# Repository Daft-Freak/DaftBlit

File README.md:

# DaftBlit
It's... a handheld console?

## Boards
- [Gamepads](https://github.com/Daft-Freak/py32-i2c-gamepad) (x2)
- `board/extra-buttons`: "Start/Select" buttons
- `board/display`: "Display" / main baard (has some sound/backlight issues)

## 3D Printed Parts
- `abxy.stl` A/B/X/Y buttons (x4)
- `console28-back.stl` back half of case
- `console28-front.stl` front half of case, should be printed face down
- `console28-dbg-cover` cover for debug port access
- `controller-mod-back.stl`/`controller-mod-front.stl` modifiers for multi-colour printing
- `dpad.stl` dpad, requires supports and a bit tricky to print
- `on-off-flat.stl` power button
- `start-select.stl` start/select buttons, requires supports and is very small (x2)

## Other hardware
- Button pads: 2x the dpad part from a GBA SP set.
- LCD: https://www.aliexpress.com/item/1005009128815676.html (2.8 inch 40 pin 240x320 ST7789)
- Speaker: TODO (can't remember if it's https://shop.pimoroni.com/products/mini-speaker-8-1w or not)
- Battery: TODO
- Screws: [TODO](assembly/00-screws2.jpeg) (there are four different ones)
- Cables: 1-2 "short" (50mm?) i2c cables and a longer one (100mm?), 5-pin 0.5mm ffc for start/select buttons
- Joystick: the switch joy-con one
- Brains: RP2350 stamp, the XL one if you want the power button to work
- Optional sensor stick for... sensors

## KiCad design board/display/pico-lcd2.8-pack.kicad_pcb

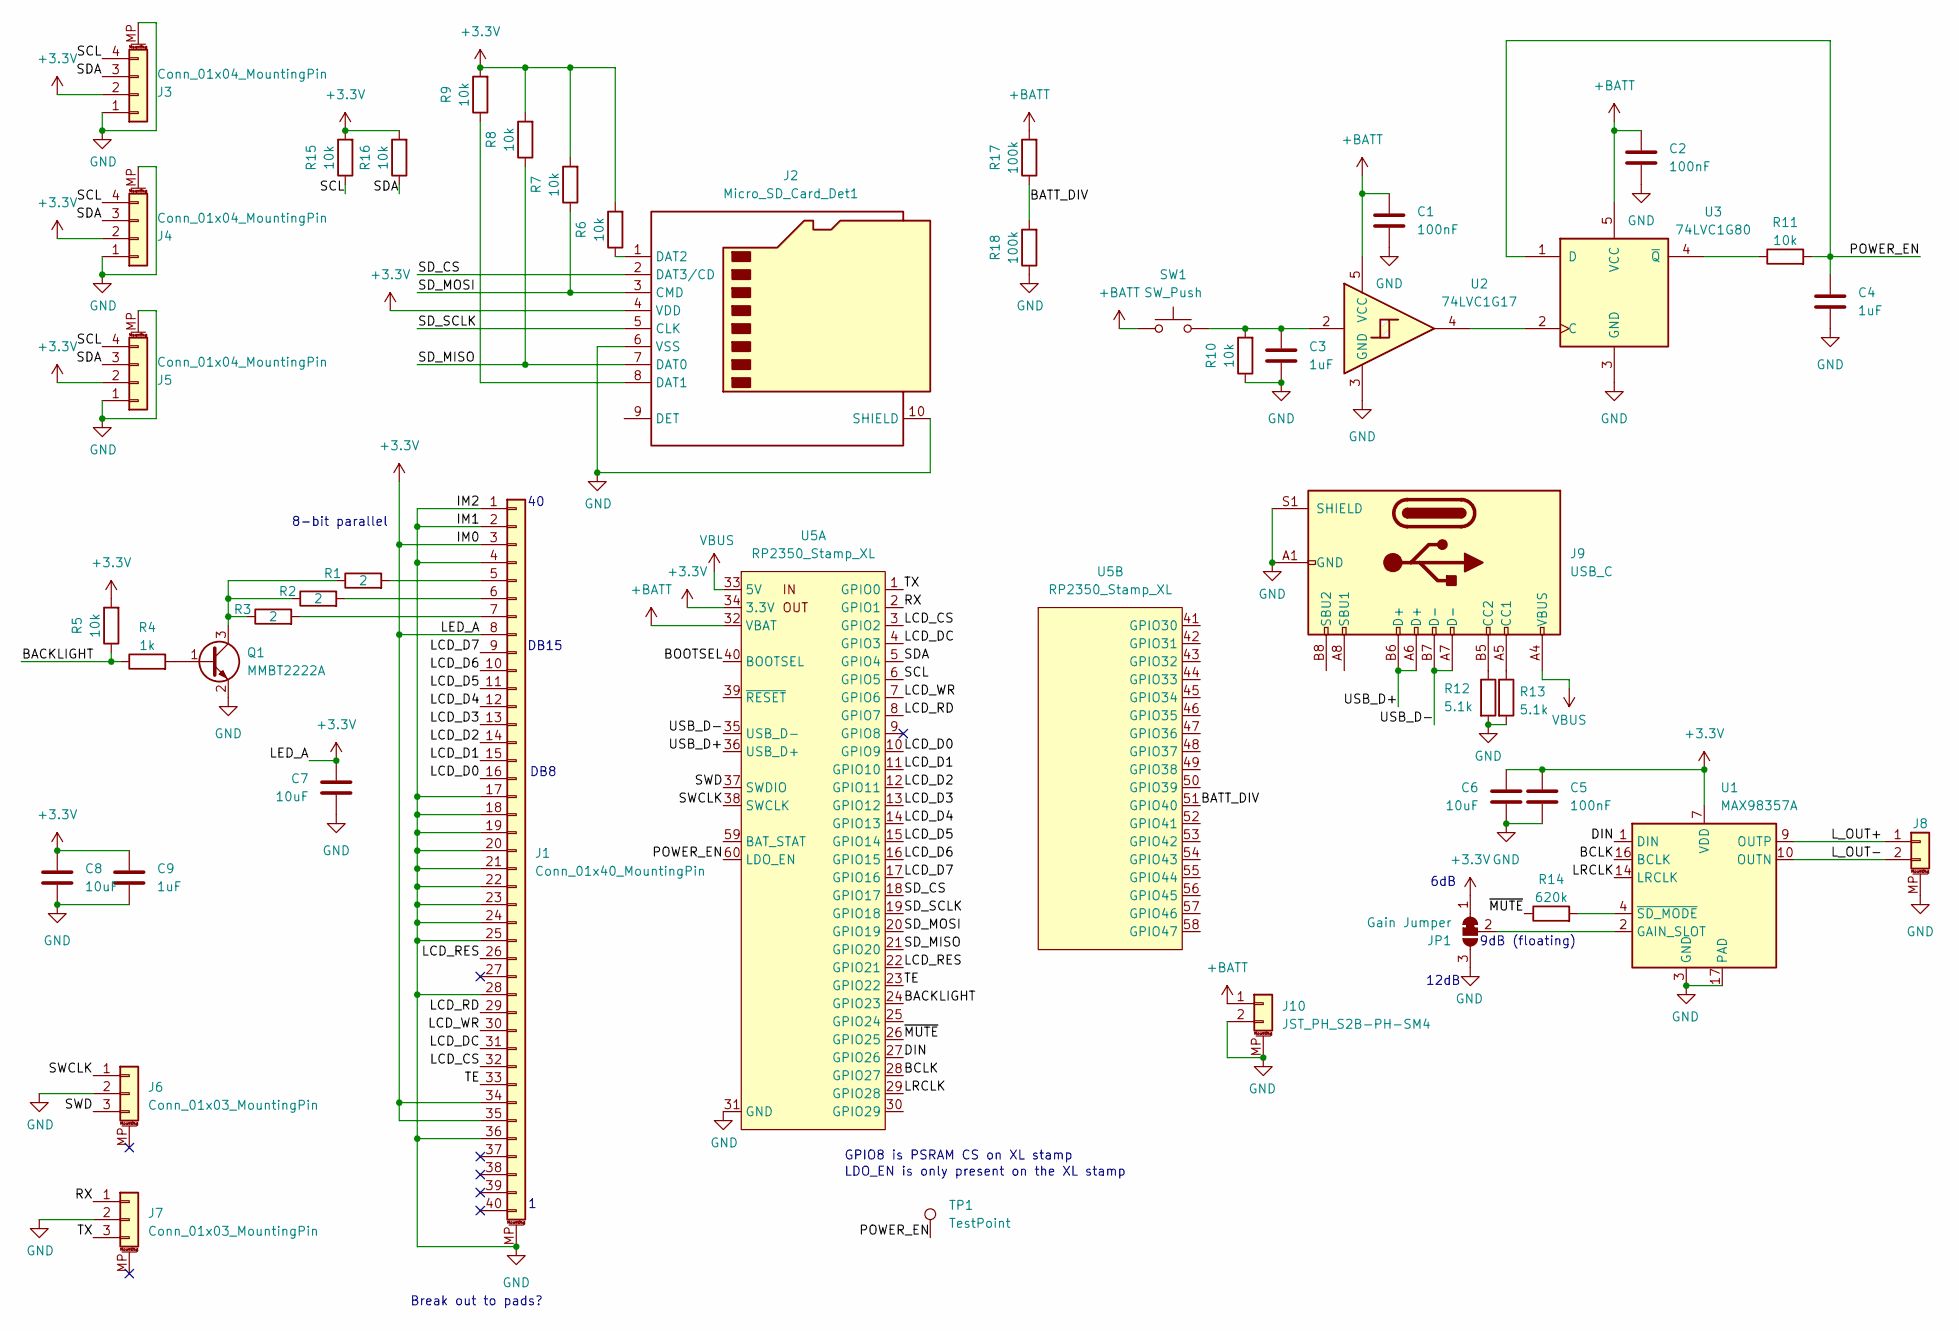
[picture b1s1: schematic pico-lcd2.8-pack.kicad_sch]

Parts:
C1, C2, C5: 100nF; C_0402_1005Metric
C3, C4, C9: 1uF; C_0402_1005Metric
C6, C7, C8: 10uF; C_0402_1005Metric
J1: Conn_01x40_MountingPin; XUNPU_FPC-05FB-40PH20_1x40-1MP_P0.50mm_Horizontal
J2: Micro_SD_Card_Det1; microSD_HC_Push
J3, J4, J5: Conn_01x04_MountingPin; JST_SH_SM04B-SRSS-TB_1x04-1MP_P1.00mm_Horizontal
J6, J7: Conn_01x03_MountingPin; JST_SH_SM03B-SRSS-TB_1x03-1MP_P1.00mm_Horizontal
J8: 1X02PICOBLADE; Molex_PicoBlade_53261-0271_1x02-1MP_P1.25mm_Horizontal
J9: USB_C; USB_C_Receptacle_HRO_TYPE-C-31-M-12
J10: JST_PH_S2B-PH-SM4; JST_PH_S2B-PH-SM4-TB_1x02-1MP_P2.00mm_Horizontal
JP1: Gain Jumper; SolderJumper-3_P1.3mm_Bridged12_RoundedPad1.0x1.5mm
Q1: MMBT2222A; SOT-23
R1, R2, R3: 2; R_0402_1005Metric
R4: 1k; R_0402_1005Metric
R5, R6, R7, R8, R9, R10, R11, R15, R16: 10k; R_0402_1005Metric
R12, R13: 5.1k; R_0402_1005Metric
R14: 620k; R_0402_1005Metric
R17, R18: 100k; R_0402_1005Metric
SW1: SW_Push; SW_Push_TSA002
TP1: TestPoint; TestPoint_Pad_1.0x1.0mm
U1: MAX98357A; TQFN-16-1EP_3x3mm_P0.5mm_EP1.23x1.23mm
U2: 74LVC1G17; SOT-353_SC-70-5
U3: 74LVC1G80; SOT-353_SC-70-5
U5: RP2350_Stamp_XL; RP2xxx_Stamp_Combo_SMD

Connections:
+3.3V: C5.1, C6.1, C7.1, C8.1, C9.1, J1.3, J1.8, J1.34, J1.35, J2.4 (VDD), J3.2, J4.2, J5.2, JP1.1 (A), R5.2, R6.2, R7.2, R8.2, R9.2, R15.2, R16.2, U1.7 (VDD), U1.8 (VDD), U5.34 (3.3V)
+BATT: C1.1, C2.1, J10.1, R17.2, SW1.1, U2.5 (VCC), U3.5 (VCC), U5.32 (VBAT)
/BACKLIGHT: R4.1, R5.1, U5.24 (GPIO23)
/BATT_DIV: R17.1, R18.2, U5.51 (GPIO40)
/BCLK: U1.16 (BCLK), U5.28 (GPIO27)
/BOOTSEL: U5.40 (BOOTSEL)
/DIN: U1.1 (DIN), U5.27 (GPIO26)
/LCD_CS: J1.32, U5.3 (GPIO2)
/LCD_D0: J1.16, U5.10 (GPIO9)
/LCD_D1: J1.15, U5.11 (GPIO10)
/LCD_D2: J1.14, U5.12 (GPIO11)
/LCD_D3: J1.13, U5.13 (GPIO12)
/LCD_D4: J1.12, U5.14 (GPIO13)
/LCD_D5: J1.11, U5.15 (GPIO14)
/LCD_D6: J1.10, U5.16 (GPIO15)
/LCD_D7: J1.9, U5.17 (GPIO16)
/LCD_DC: J1.31, U5.4 (GPIO3)
/LCD_RD: J1.29, U5.8 (GPIO7)
/LCD_RES: J1.26, U5.22 (GPIO21)
/LCD_WR: J1.30, U5.7 (GPIO6)
/LRCLK: U1.14 (LRCLK), U5.29 (GPIO28)
/L_OUT+: J8.1, U1.9 (OUTP)
/L_OUT-: J8.2, U1.10 (OUTN)
/POWER_EN: C4.1, R11.2, TP1.1, U3.1 (D), U5.60 (LDO_EN)
/RX: J7.1, U5.2 (GPIO1)
/SCL: J3.4, J4.4, J5.4, R15.1, U5.6 (GPIO5)
/SDA: J3.3, J4.3, J5.3, R16.1, U5.5 (GPIO4)
/SD_CS: J2.2 (DAT3/CD), U5.18 (GPIO17)
/SD_MISO: J2.7 (DAT0), R8.1, U5.21 (GPIO20)
/SD_MOSI: J2.3 (CMD), R7.1, U5.20 (GPIO19)
/SD_SCLK: J2.5 (CLK), U5.19 (GPIO18)
/SWCLK: J6.1, U5.38 (SWCLK)
/SWD: J6.3, U5.37 (SWDIO)
/TE: J1.33, U5.23 (GPIO22)
/TX: J7.3, U5.1 (GPIO0)
/USB_D+: J9.A6 (D+), J9.B6 (D+), U5.36 (USB_D+)
/USB_D-: J9.A7 (D-), J9.B7 (D-), U5.35 (USB_D-)
/~MUTE: R14.1, U5.26 (GPIO25)
GND: C1.2, C2.2, C3.2, C4.2, C5.2, C6.2, C7.2, C8.2, C9.2, J1.1, J1.2, J1.4, J1.17, J1.18, J1.19, J1.20, J1.21, J1.22, J1.23, J1.24, J1.25, J1.28, J1.36, J1.MP (MountPin), J2.6 (VSS), J2.10 (SHIELD), J3.1, J3.MP (MountPin), J4.1, J4.MP (MountPin), J5.1, J5.MP (MountPin), J6.2, J7.2, J8.MP (MountPin), J9.A1 (GND), J9.A12 (GND), J9.B1 (GND), J9.B12 (GND), J9.S1 (SHIELD), J10.2, J10.MP (MountPin), JP1.3 (B), Q1.2 (E), R10.1, R12.2, R13.2, R18.1, U1.3 (GND), U1.11 (GND), U1.15 (GND), U1.17 (PAD), U2.3 (GND), U3.3 (GND), U5.31 (GND)
unnamed: C3.1, R10.2, SW1.2, U2.2
unnamed: J1.5, R1.2
unnamed: J1.6, R2.2
unnamed: J1.7, R3.2
unnamed: J2.8 (DAT1), R9.1
unnamed: J2.1 (DAT2), R6.1
unnamed: J9.A5 (CC1), R13.1
unnamed: J9.B5 (CC2), R12.1
unnamed: JP1.2 (C), U1.2 (GAIN_SLOT)
unnamed: Q1.1 (B), R4.2
unnamed: Q1.3 (C), R1.1, R2.1, R3.1
unnamed: R14.2, U1.4 (~SD_MODE)
unnamed: U2.4, U3.2 (C)
unnamed: R11.1, U3.4 (~Q)
VBUS: J9.A4 (VBUS), J9.A9 (VBUS), J9.B4 (VBUS), J9.B9 (VBUS), U5.33 (5V)

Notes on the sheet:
LDO_EN is only present on the XL stamp
6dB
GPIO8 is PSRAM CS on XL stamp
8-bit parallel
Break out to pads?
12dB
9dB (floating)
DB15
DB8

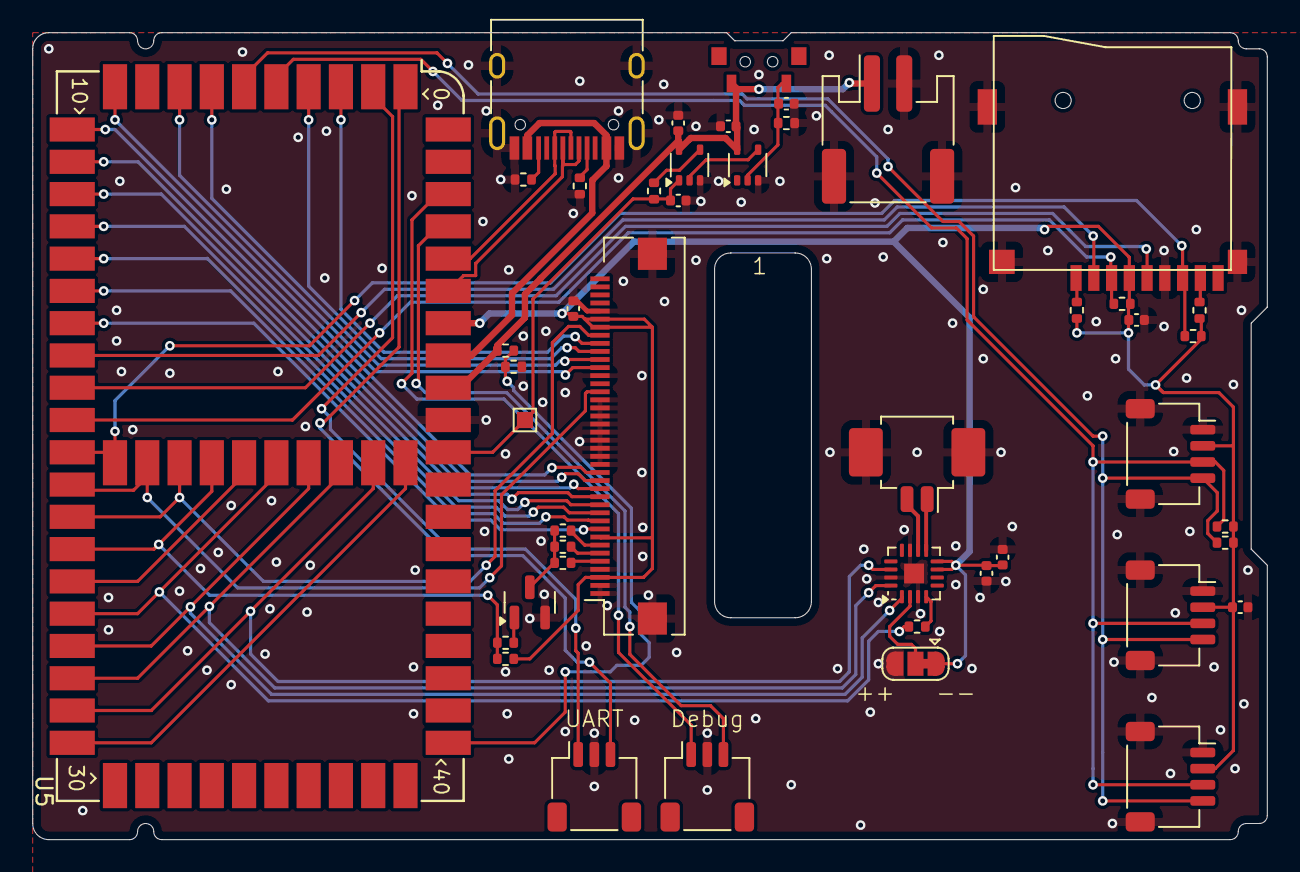
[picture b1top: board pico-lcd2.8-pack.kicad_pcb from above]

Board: 2 copper layers, 76.5 x 50.0 mm, 45 parts (0 on the bottom side), 53 nets.

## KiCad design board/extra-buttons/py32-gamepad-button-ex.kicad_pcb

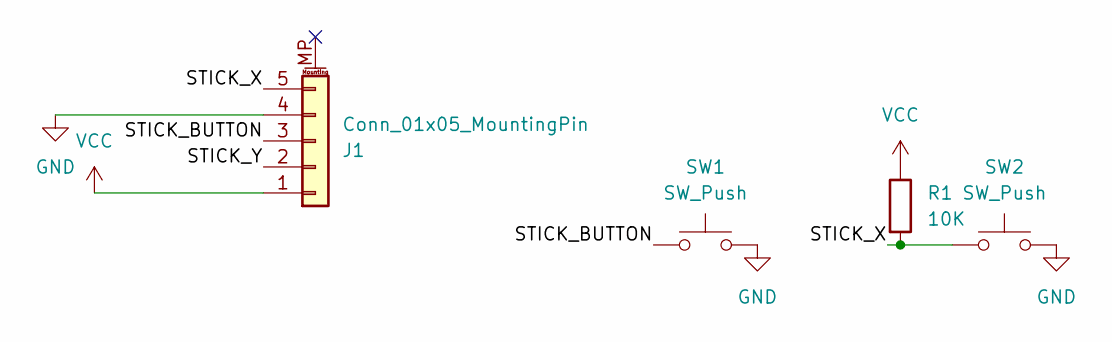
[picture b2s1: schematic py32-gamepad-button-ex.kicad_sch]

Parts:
J1: Conn_01x05_MountingPin; HCTL_HC-FPC-05-09-5RLTAG-00_1x05-1MP_P0.50mm_Horizontal
R1: 10K; R_0402_1005Metric
SW1, SW2: SW_Push; SW_Push_1P1T_NO_TSC001

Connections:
/STICK_BUTTON: J1.3, SW1.1
/STICK_X: J1.5, R1.2, SW2.1
/STICK_Y: J1.2
GND: J1.4, SW1.2, SW2.2
VCC: J1.1, R1.1

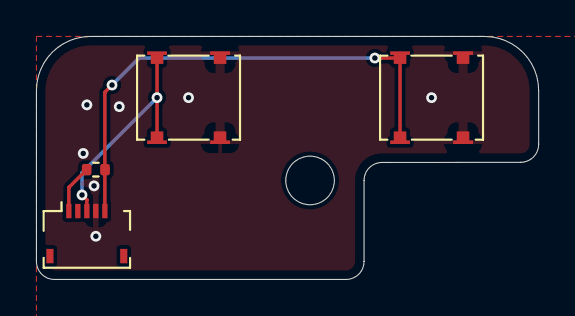
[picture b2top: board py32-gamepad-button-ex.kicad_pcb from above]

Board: 2 copper layers, 27.9 x 13.5 mm, 4 parts (0 on the bottom side), 4 nets.

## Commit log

2025-07-05 Add link to the gamepads
    The one thing that's already out there
2025-07-05 Add 3d-printed parts
2025-07-05 More README
    At least what I can remember right now
2025-07-06 Some photos of parts
2025-07-06 Photos of assembled boards
2025-07-06 Some assembly
2025-07-06 Fix 09 orientation
2025-07-06 Add "extra buttons" board
    This one is straightforward...
2025-07-07 Extra buttons are there now
2025-07-07 Add the "display" board
    I think this is the current version, sound/backlight issues included...
2025-07-08 Add a photo of the thing
2025-07-08 Fix 02 orientation
2025-07-08 Start assembling the assembly photos
2025-07-08 Fix image paths
    The preview lied!
